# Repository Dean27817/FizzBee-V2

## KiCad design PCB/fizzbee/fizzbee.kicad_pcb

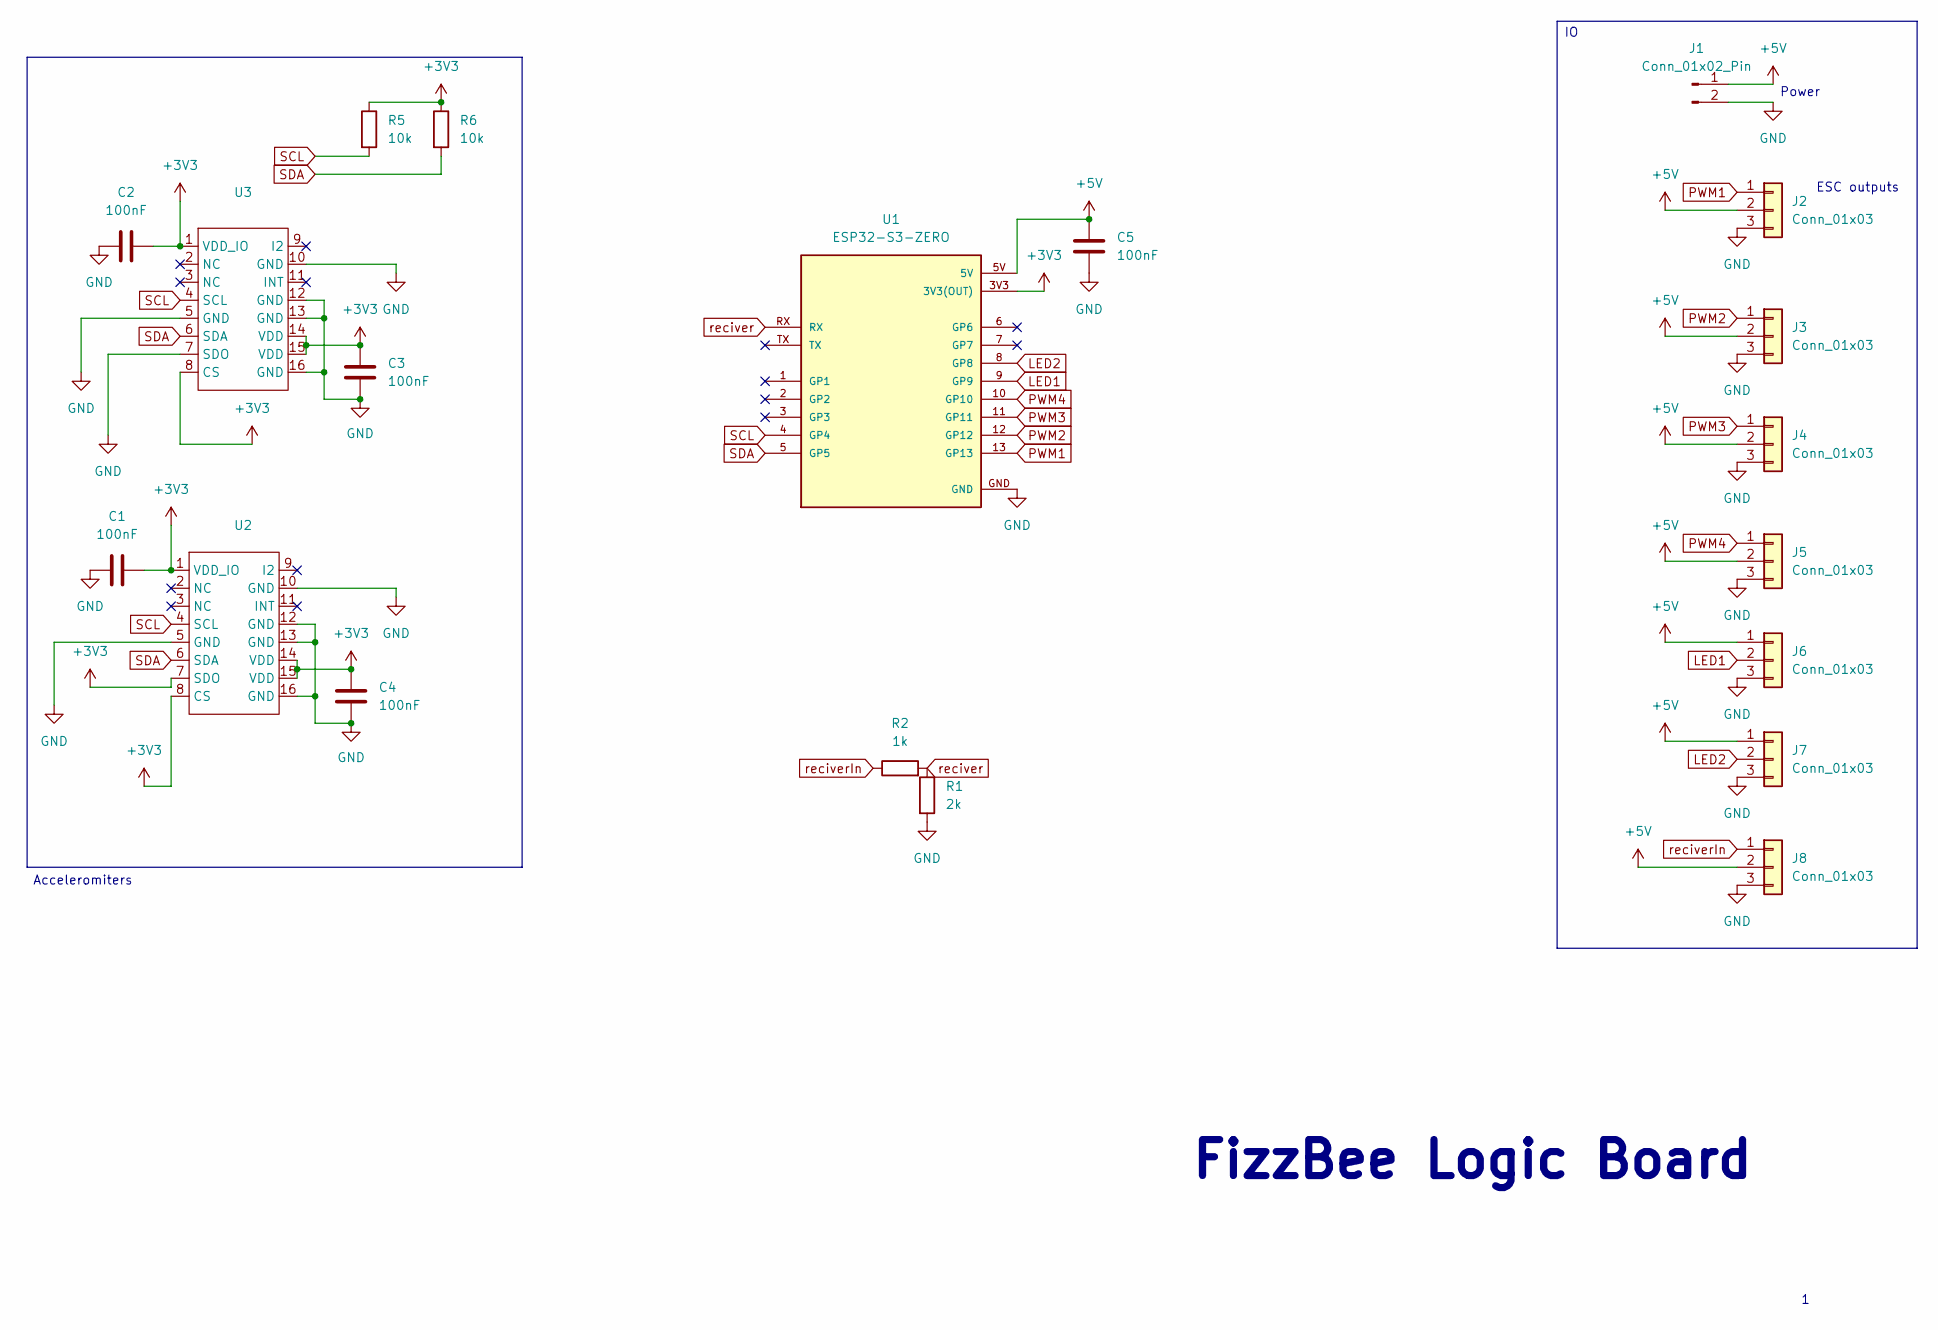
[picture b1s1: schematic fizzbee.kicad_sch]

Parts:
C1, C2, C3, C4, C5: 100nF; C_0402_1005Metric
J1: Conn_01x02_Pin; PinHeader_1x02_P2.54mm_Vertical
J2, J3, J4, J5, J6, J7, J8: Conn_01x03; PinHeader_1x03_P2.54mm_Vertical
R1: 2k; C_0402_1005Metric
R2: 1k; C_0402_1005Metric
R5, R6: 10k; C_0402_1005Metric
U1: ESP32-S3-ZERO; MODULE_ESP32-S3-ZERO; PARTREV NA
U2, U3: QFN300X300X100-16N

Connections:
+3V3: C1.2, C2.2, C3.1, C4.1, R5.1, R6.1, U1.3V3 (3V3(OUT)), U2.1 (VDD_IO), U2.7 (SDO), U2.8 (CS), U2.14 (VDD), U2.15 (VDD), U3.1 (VDD_IO), U3.8 (CS), U3.14 (VDD), U3.15 (VDD)
+5V: C5.1, J1.1, J2.2, J3.2, J4.2, J5.2, J6.1, J7.1, J8.2, U1.5V
GND: C1.1, C2.1, C3.2, C4.2, C5.2, J1.2, J2.3, J3.3, J4.3, J5.3, J6.3, J7.3, J8.3, R1.2, U1.GND, U2.5 (GND), U2.10 (GND), U2.12 (GND), U2.13 (GND), U2.16 (GND), U3.5 (GND), U3.7 (SDO), U3.10 (GND), U3.12 (GND), U3.13 (GND), U3.16 (GND)
LED1: J6.2, U1.9 (GP9)
LED2: J7.2, U1.8 (GP8)
PWM1: J2.1, U1.13 (GP13)
PWM2: J3.1, U1.12 (GP12)
PWM3: J4.1, U1.11 (GP11)
PWM4: J5.1, U1.10 (GP10)
SCL: R5.2, U1.4 (GP4), U2.4 (SCL), U3.4 (SCL)
SDA: R6.2, U1.5 (GP5), U2.6 (SDA), U3.6 (SDA)
reciver: R1.1, R2.2, U1.RX
reciverIn: J8.1, R2.1

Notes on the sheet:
ESC outputs
FizzBee Logic Board
Power
Acceleromiters

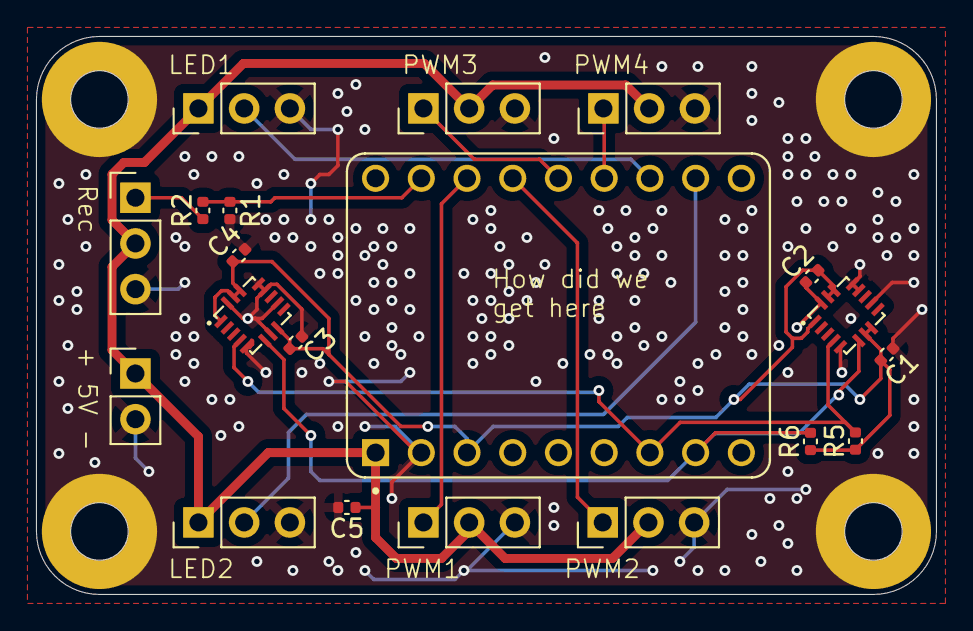
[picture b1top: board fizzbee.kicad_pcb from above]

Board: 2 copper layers, 50.0 x 31.0 mm, 20 parts (0 on the bottom side), 13 nets.

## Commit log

2025-12-23 Added initial code
2026-01-07 Moved changes form HDD
2026-01-07 modified: code/.gitignore
2026-01-07 Added OTA back in
2026-01-07 changed main to fit new functions
